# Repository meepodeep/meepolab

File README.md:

# MeepoLab
## Beginner 25-key midi controller with velocity-sensitive keys and drum pads

## Why does this exist
I made this project because I have been recently getting into making music for my own games, but I got tired of using a keyboard to do everything, so when Hackclub Stasis started to exist, I decided to make this. 
midi controller
# How to build
## PCB
1. Lay out and solder all of the smd components to the board
2. Solder the jst connectors
3. Solder the teensy on with pin headers
4. Flash the meepolab_sketch.ino file onto the teensy using midi mode
## Wiring 2
1. Solder the wires of the 12 pin jst connectors to all of the key matrix tactile switches and plug them into the plugs with these numbers. wire the "bottom" tactile switches to be the ones furthest from the pivot of the key, and the "top" ones closest to the center of the key. ( DO THIS AFTER YOU MOUNT THEM )
2. The V and ground are the 2 pins on the tactile switches, not actual voltage and ground
3. 
4. Solder the rest of your inputs, potentiometer, slide pot to the other 12pin jst connectors and plug them into the plugs with these numbers
5. 
6. Solder these jst connectors to the piezo drum pad sensors  and plug them into the plugs with these numbers
7. 
8. Solder the leds to the led jst connectors and plug them into the plugs with these numbers

## Assembly
1. assemble the 4 parts of the main shell and backplate together
2. Insert a bearing into the hole of every key
3. 
4. Align all of the keys how they are supposed to be and push the rod through the case,  bearings and keys
5. insert all of the return springs in between the pegs on the case and every key
6. 
7.insert all of the tactile switches into their holes in their mounting brackets.

8. tape piezo sensors to the back of each drum pad square on the drum pad membrane and the leds from the first shift register to it as well, and then mount the drum pad membrane to the keyboard
9. 
10. Mount the octave rocker, first by inserting it into position, and then inserting the axel after
11. 
12. insert a keyswitch into each of the octave rocker keyswitch mounts square holes and then screw them in using m3 hardware
13.
14. insert the keyswitches for the shift pause/play and record buttons into their holes
15. 
16. insert the potentiometers into their holes and screw them down using the included nut, after inserting the potentiometer area accent
17. 
18. put on the potentiometer caps
19. insert the slide potentiometers and screw in using m3 hardware after inserting accents
20. 
21. put on fader caps
22. insert leds and cover with optional acrylic
23. \
24. connect the cable to the teensy and run it through the hole
25. Attach bottom with m3 hardware
26. 
27. put keycaps on keys if you want
28. 

# BOM

|Name                |Purpose                                |Quantity|Total Cost (USD)|Link                                                                                                                                                                                                                                                                                                                                                                                                                                                                                                                                                                                                                                                                           |Distributor|
|--------------------|---------------------------------------|--------|----------------|-------------------------------------------------------------------------------------------------------------------------------------------------------------------------------------------------------------------------------------------------------------------------------------------------------------------------------------------------------------------------------------------------------------------------------------------------------------------------------------------------------------------------------------------------------------------------------------------------------------------------------------------------------------------------------|-----------|
|blue leds           |wie cool ist das bitte (it look pretty)|1       |1.42            |https://www.aliexpress.us/item/3256805214023855.html?spm=a2g0o.productlist.main.11.27da247cc44Ob9&algo_pvid=6ad9489b-c67a-4f82-b179-5dc6dc1113cd&algo_exp_id=6ad9489b-c67a-4f82-b179-5dc6dc1113cd-10&pdp_ext_f=%7B%22order%22%3A%22201%22%2C%22eval%22%3A%221%22%2C%22fromPage%22%3A%22search%22%7D&pdp_npi=6%40dis%21USD%211.54%211.54%21%21%211.54%211.54%21%40210319b017754310480521908e388a%2112000032909655679%21sea%21US%214381910819%21X%211%210%21n_tag%3A-29919%3Bd%3A747bdf24%3Bm03_new_user%3A-29895&curPageLogUid=ZzhfMunGS7JW&utparam-url=scene%3Asearch%7Cquery_from%3A%7Cx_object_id%3A1005005400338607%7C_p_origin_prod%3A                                     |aliexpress |
|acrylic             |optional led diffuse                   |1       |0.00            |                                                                                                                                                                                                                                                                                                                                                                                                                                                                                                                                                                                                                                                                               |i have     |
|keycap              |capping keys                           |3       |0.00            |                                                                                                                                                                                                                                                                                                                                                                                                                                                                                                                                                                                                                                                                               |i have     |
|m3 hardware         |hardware                               |1       |0.00            |                                                                                                                                                                                                                                                                                                                                                                                                                                                                                                                                                                                                                                                                               |i have     |
|mx keyswitches      |buttons                                |5       |0.00            |                                                                                                                                                                                                                                                                                                                                                                                                                                                                                                                                                                                                                                                                               |i have     |
|tactile swtiches    |For keys                               |3       |6.72            |https://www.aliexpress.us/item/2251832777534166.html?spm=a2g0o.productlist.main.18.2eb47bd6MNSk1R&algo_pvid=fd58ec73-369f-4c27-952a-6fe7ae065374&algo_exp_id=fd58ec73-369f-4c27-952a-6fe7ae065374-17&pdp_ext_f=%7B%22order%22%3A%22311%22%2C%22spu_best_type%22%3A%22price%22%2C%22eval%22%3A%221%22%2C%22fromPage%22%3A%22search%22%7D&pdp_npi=6%40dis%21USD%212.24%212.24%21%21%212.24%212.24%21%402101e2b217754281745518955efc8b%2166540730075%21sea%21US%214381910819%21X%211%210%21n_tag%3A-29919%3Bd%3A747bdf24%3Bm03_new_user%3A-29895&curPageLogUid=oJnjzIDFX0Vx&utparam-url=scene%3Asearch%7Cquery_from%3A%7Cx_object_id%3A32963848918%7C_p_origin_prod%3A            |aliexpress |
|12pin jst           |wiring keyswitches                     |3       |9.96            |https://www.aliexpress.us/item/3256811409118695.html?spm=a2g0o.detail.0.0.6681x6iXx6iXXv&mp=1&pdp_npi=6%40dis%21USD%21USD+10.11%21USD+4.42%21%21USD+4.09%21%21%21%4021033d1217779309699333617edbad%2112000056013353219%21ct%21US%214381910819%21%213%210%21&gatewayAdapt=glo2usa                                                                                                                                                                |aliexpress |
|Jst Ph2.0 2pin      |leds                                   |2       |5.36            |https://www.aliexpress.us/item/3256809537971085.html?spm=a2g0o.productlist.main.1.66a4xxW3xxW33G&algo_pvid=53bc2f55-a166-4808-bcda-89f28673fb9f&algo_exp_id=53bc2f55-a166-4808-bcda-89f28673fb9f-0&pdp_ext_f=%7B%22order%22%3A%22404%22%2C%22spu_best_type%22%3A%22price%22%2C%22eval%22%3A%221%22%2C%22fromPage%22%3A%22search%22%7D&pdp_npi=6%40dis%21USD%213.94%212.68%21%21%213.94%212.68%21%40210311cc17754258341333693e44fb%2112000049958235025%21sea%21US%214381910819%21X%211%210%21n_tag%3A-29919%3Bd%3A747bdf24%3Bm03_new_user%3A-29895&curPageLogUid=gRPF38s0QkMk&utparam-url=scene%3Asearch%7Cquery_from%3A%7Cx_object_id%3A1005009724285837%7C_p_origin_prod%3A   |aliexpress |
|Pcb                 |wiring up everythign                   |5       |28.60           |                                                                                                                                                                                                                                                                                                                                                                                                                                                                                                                                                                                                                                                                               |jlcpcb     |
|Teensy 4.1          |microcontroller                        |1       |31.50           |https://www.robotshop.com/products/teensy-41-usb-microcontroller-development-board-no-pins                                                                                                                                                                                                                                                                                                                                                                                                                                                                                                                                                                                     |RobotShop  |
|micro b to usb cable|cable for output                       |1       |2.34            |https://www.aliexpress.us/item/3256811607885785.html?spm=a2g0o.productlist.main.3.1e6bQvSEQvSEZj&algo_pvid=67884bd9-509c-4024-8bfe-0b6e9d9e573c&algo_exp_id=67884bd9-509c-4024-8bfe-0b6e9d9e573c-2&pdp_ext_f=%7B%22order%22%3A%2221%22%2C%22eval%22%3A%221%22%2C%22fromPage%22%3A%22search%22%7D&pdp_npi=6%40dis%21USD%214.36%212.01%21%21%2129.85%2113.76%21%40210311cc17752395169437863e44cf%2112000056573607707%21sea%21US%214381910819%21X%211%210%21n_tag%3A-29919%3Bd%3A5f7e402d%3Bm03_new_user%3A-29895%3BpisId%3A5000000203713564&curPageLogUid=mdmygZeXfOSF&utparam-url=scene%3Asearch%7Cquery_from%3A%7Cx_object_id%3A1005011794200537%7C_p_origin_prod%3A           |Aliexpress |
|45mm slide pot      |faders                                 |1       |2.63            |https://www.aliexpress.us/item/3256808869794293.html?spm=a2g0o.productlist.main.2.74107820OVm44F&algo_pvid=9917adf3-acb4-4790-a7cf-8f4ffd8a9d8e&algo_exp_id=9917adf3-acb4-4790-a7cf-8f4ffd8a9d8e-1&pdp_ext_f=%7B%22order%22%3A%22255%22%2C%22eval%22%3A%221%22%2C%22fromPage%22%3A%22search%22%7D&pdp_npi=6%40dis%21USD%216.27%212.63%21%21%2142.95%2118.04%21%402101f54117751893635285930efa7d%2112000047742701705%21sea%21US%214381910819%21X%211%210%21n_tag%3A-29919%3Bd%3A5f7e402d%3Bm03_new_user%3A-29895&curPageLogUid=GEGioSHPormD&utparam-url=scene%3Asearch%7Cquery_from%3A%7Cx_object_id%3A1005009056109045%7C_p_origin_prod%3A                                     |Aliexpress |
|10k pot             |dials                                  |2       |3.94            |https://www.aliexpress.us/item/3256802975243588.html?spm=a2g0o.productlist.main.2.7c453333dXrhMZ&algo_pvid=5c2d9dee-aaee-460d-8edb-a6a78972ec2f&algo_exp_id=5c2d9dee-aaee-460d-8edb-a6a78972ec2f-1&pdp_ext_f=%7B%22order%22%3A%221037%22%2C%22eval%22%3A%221%22%2C%22fromPage%22%3A%22search%22%7D&pdp_npi=6%40dis%21USD%212.08%211.96%21%21%212.08%211.96%21%40210337c117751859745701587eadbd%2112000024425220404%21sea%21US%214381910819%21X%211%210%21n_tag%3A-29919%3Bd%3A5f7e402d%3Bm03_new_user%3A-29895%3BpisId%3A5000000203818699&curPageLogUid=UUUgrKTkZwgk&utparam-url=scene%3Asearch%7Cquery_from%3A%7Cx_object_id%3A1005003161558340%7C_p_origin_prod%3A           |Aliexpress |
|Piezo sensor 12mm   |drum pads                              |1       |2.35            |https://www.aliexpress.us/item/3256806816727111.html?spm=a2g0o.productlist.main.7.43d97c70RlzFL1&algo_pvid=773ae987-53a6-4b90-81c1-8f194f19a3d9&algo_exp_id=773ae987-53a6-4b90-81c1-8f194f19a3d9-6&pdp_ext_f=%7B%22order%22%3A%221204%22%2C%22spu_best_type%22%3A%22price%22%2C%22eval%22%3A%221%22%2C%22fromPage%22%3A%22search%22%7D&pdp_npi=6%40dis%21USD%212.35%212.35%21%21%2116.09%2116.09%21%40210337c117751854355162761eadb5%2112000039015286338%21sea%21US%214381910819%21X%211%210%21n_tag%3A-29919%3Bd%3A5f7e402d%3Bm03_new_user%3A-29895&curPageLogUid=E22xylpVI4bu&utparam-url=scene%3Asearch%7Cquery_from%3A%7Cx_object_id%3A1005007003041863%7C_p_origin_prod%3A|Aliexpress |
|15x8mm spring       |key return                             |3       |13.48           |https://www.aliexpress.us/item/3256807447886846.html?spm=a2g0o.productlist.main.1.6c23783cb5SKfr&algo_pvid=ed966f8d-a3aa-4052-a5ed-c99569bf1975&algo_exp_id=ed966f8d-a3aa-4052-a5ed-c99569bf1975-0&pdp_ext_f=%7B%22order%22%3A%2272%22%2C%22eval%22%3A%221%22%2C%22fromPage%22%3A%22search%22%7D&pdp_npi=6%40dis%21USD%213.18%213.08%21%21%2121.81%2121.11%21%40210337c117751740330991406eadc8%2112000041585331673%21sea%21US%214381910819%21X%211%210%21n_tag%3A-29919%3Bd%3A5f7e402d%3Bm03_new_user%3A-29895&curPageLogUid=wyxdnGUcsvBT&utparam-url=scene%3Asearch%7Cquery_from%3A%7Cx_object_id%3A1005007634201598%7C_p_origin_prod%3A                                      |Aliexpress |
|6X10X3 bearing      |key bearings                           |3       |13.95           |https://www.aliexpress.us/item/3256810378046508.html?spm=a2g0o.productlist.main.7.22243b11uhPXbH&algo_pvid=685b833c-7b74-4b83-a32a-719ad60603e5&algo_exp_id=685b833c-7b74-4b83-a32a-719ad60603e5-6&pdp_ext_f=%7B%22order%22%3A%22509%22%2C%22eval%22%3A%221%22%2C%22fromPage%22%3A%22search%22%7D&pdp_npi=6%40dis%21USD%213.81%213.79%21%21%2126.08%2125.92%21%4021030a4b17751710399248378e75a4%2112000052831084350%21sea%21US%214381910819%21X%211%210%21n_tag%3A-29919%3Bd%3A5f7e402d%3Bm03_new_user%3A-29895&curPageLogUid=wu6zyN0LX0XR&utparam-url=scene%3Asearch%7Cquery_from%3A%7Cx_object_id%3A1005010564361260%7C_p_origin_prod%3A                                     |aliexpress |
|74HC595S16-13       |shift register for leds                |4       |1.44            |https://www.digikey.com/en/products/detail/diodes-incorporated/74HC595S16-13/24630355                                                                                                                                                                                                                                                                                                                                                                                                                                                                                                                                                                                          |Digikey    |
|RC0402FR-071ML      |resistor for piezo                     |10      |0.03            |https://www.digikey.com/en/products/detail/yageo/RC0402FR-071ML/726515                                                                                                                                                                                                                                                                                                                                                                                                                                                                                                                                                                                                         |Digikey    |
|CRT0805-BY-1500ELF  |Resistor for multiplexers              |2       |0.74            |https://www.digikey.com/en/products/detail/bourns-inc/CRT0805-BY-1500ELF/2564111                                                                                                                                                                                                                                                                                                                                                                                                                                                                                                                                                                                               |Digikey    |
|1N4148WS            |Key grid diode                         |70      |3.64            |https://www.digikey.com/en/products/detail/evvo/1N4148WS/21407535                                                                                                                                                                                                                                                                                                                                                                                                                                                                                                                                                                                                              |Digikey    |
|MMSZ4684T1G         |zener diode for piezo sensors          |10      |0.79            |https://www.digikey.com/en/products/detail/onsemi/MMSZ4684T1G/919718                                                                                                                                                                                                                                                                                                                                                                                                                                                                                                                                                                                             |Digikey    |
|SD103AW-7-F         |Schottky diode for piezo sensors       |20      |1.60            |https://www.digikey.com/en/products/detail/diodes-incorporated/SD103AW-7-F/1306103                                                                                                                                                                                                                                                                                                                                                                                                                                                                                                                                                                                             |Digikey    |
|4.7 nf capacitor    |Pcb                                    |10      |2.81            |https://www.digikey.com/en/products/detail/murata-electronics/GRM31BR72J472KW01L/789415                                                                                                                                                                                                                                                                                                                                                                                                                                                                                                                                                                                        |Digikey    |
|0.1uf capacitor     |pcb                                    |10      |0.12            |https://www.digikey.com/en/products/detail/murata-electronics/GRM033C71C104KE14D/5026260                                                                                                                                                                                                                                                                                                                                                                                                                                                                                                                                                                                       |Digikey    |

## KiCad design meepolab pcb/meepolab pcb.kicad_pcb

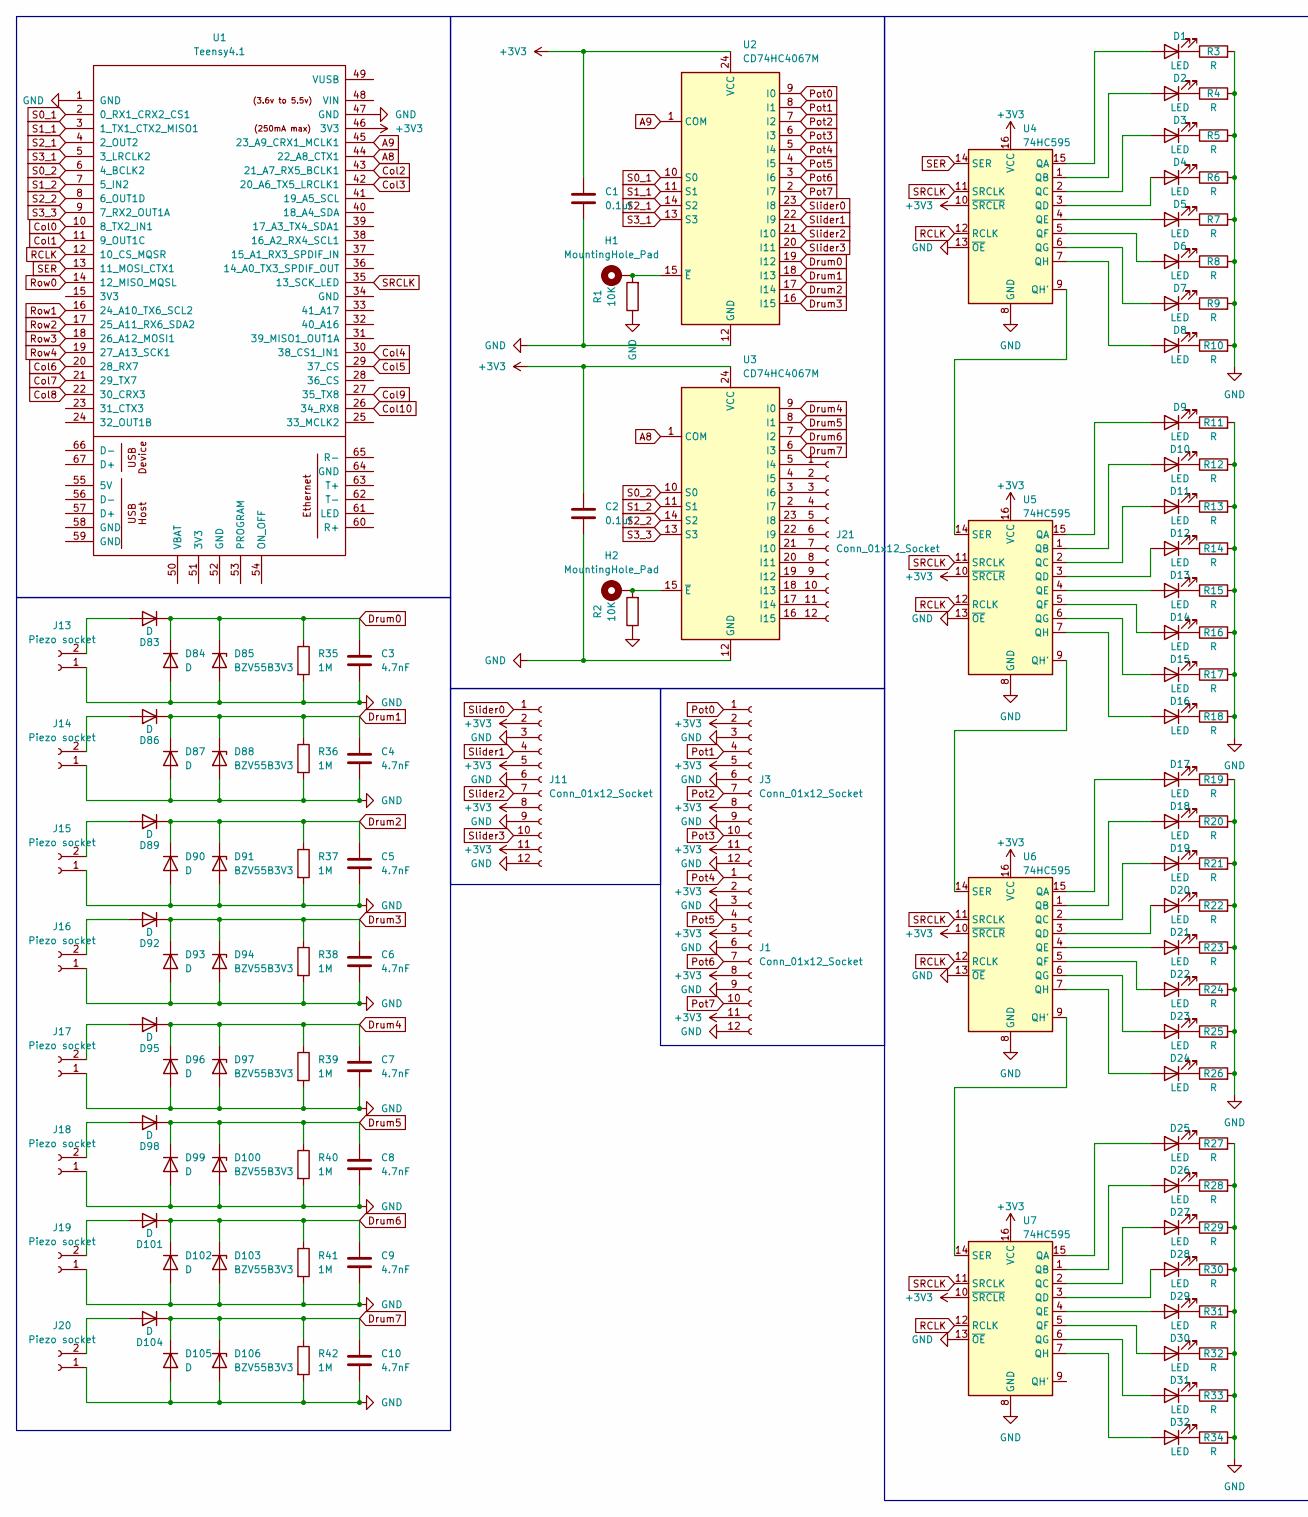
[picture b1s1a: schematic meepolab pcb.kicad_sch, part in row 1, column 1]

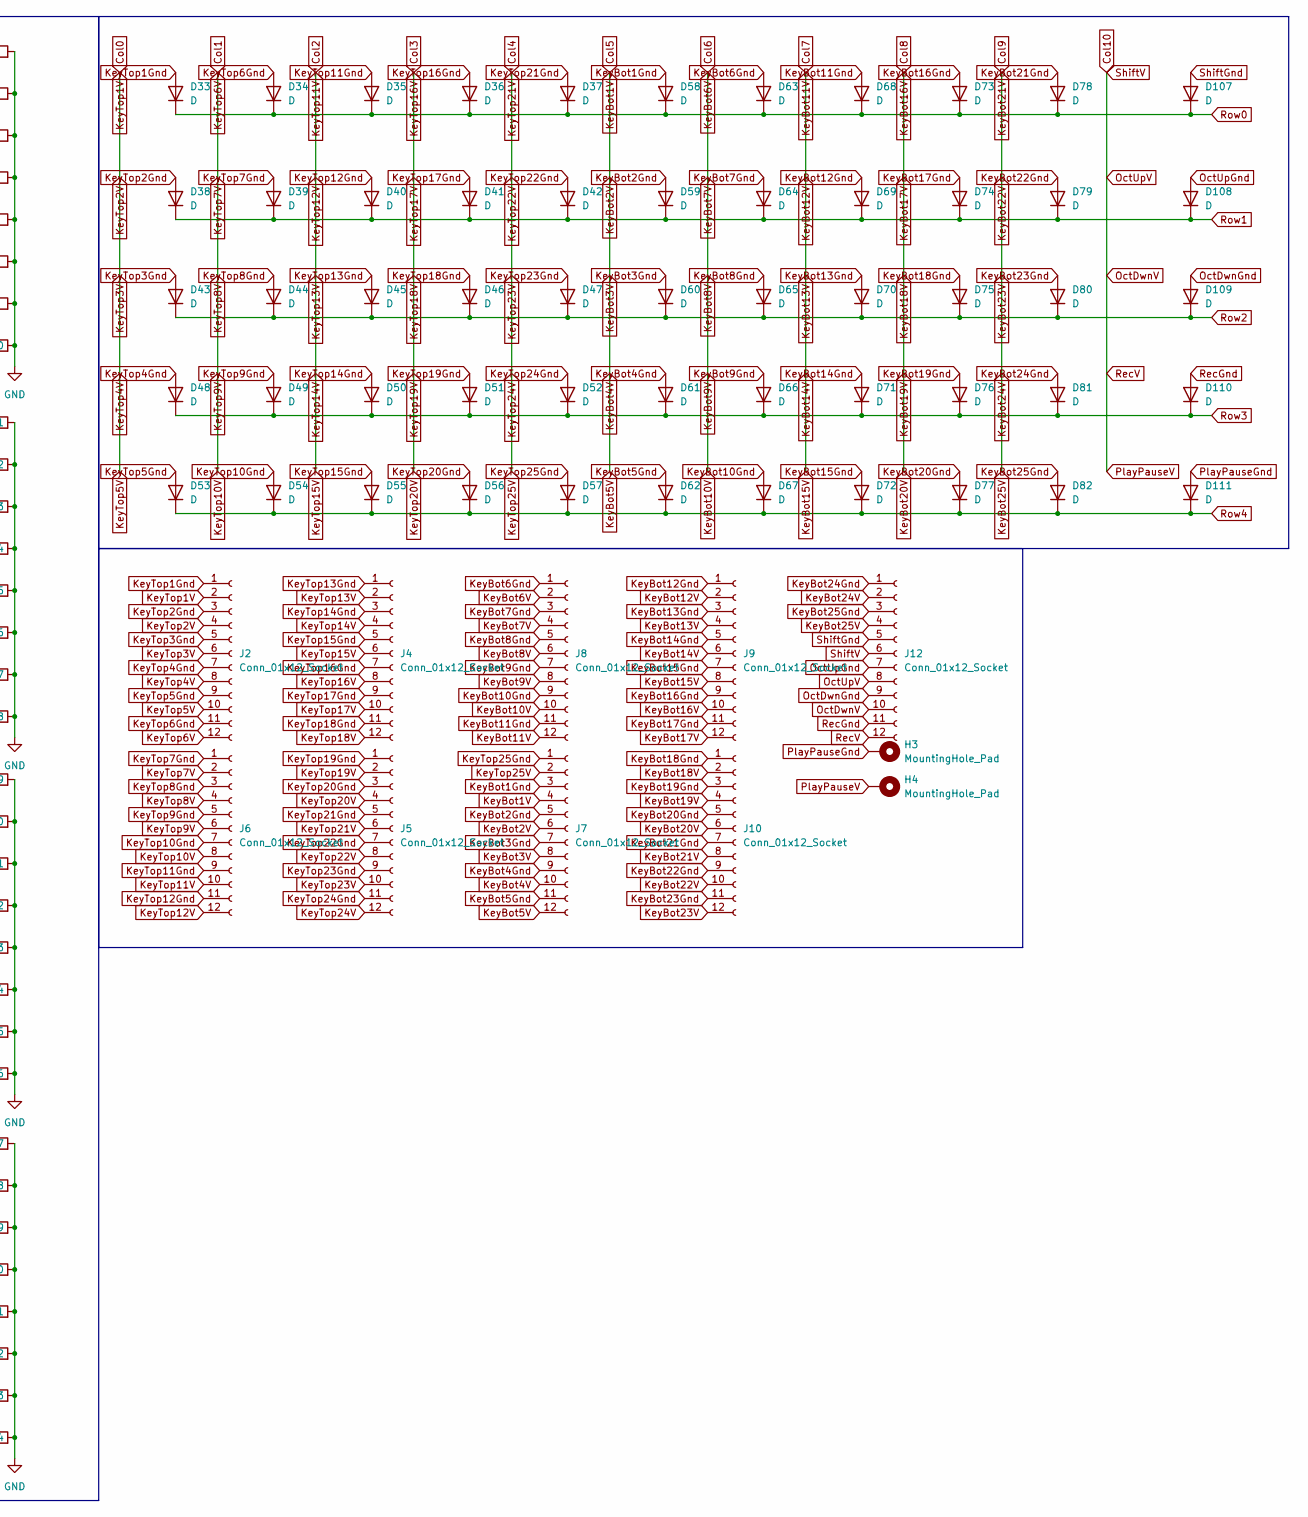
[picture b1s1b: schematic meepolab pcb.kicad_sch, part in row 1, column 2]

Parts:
C1, C2: 0.1uf; C_0201_0603Metric
C3, C4, C5, C6, C7, C8, C9, C10: 4.7nF; C_0201_0603Metric
D1, D2, D3, D4, D5, D6, D7, D8, D9, D10, D11, D12, D13, D14, D15, D16, D17, D18, D19, D20, D21, D22, D23, D24, D25, D26, D27, D28, D29, D30, D31, D32: LED; JST_EH_B2B-EH-A_1x02_P2.50mm_Vertical
D33, D34, D35, D36, D37, D38, D39, D40, D41, D42, D43, D44, D45, D46, D47, D48, D49, D50, D51, D52, D53, D54, D55, D56, D57, D58, D59, D60, D61, D62, D63, D64, D65, D66, D67, D68, D69, D70, D71, D72, D73, D74, D75, D76, D77, D78, D79, D80, D81, D82, D107, D108, D109, D110, D111: D; D_SOD-323
D83, D84, D86, D87, D89, D90, D92, D93, D95, D96, D98, D99, D101, D102, D104, D105: D; D_SOD-123
D85, D88, D91, D94, D97, D100, D103, D106: BZV55B3V3; D_SOD-123
H1, H2, H3, H4: MountingHole_Pad; TestPoint_Pad_1.0x1.0mm
J1, J2, J3, J4, J5, J6, J7, J8, J9, J10, J11, J12, J21: Conn_01x12_Socket; JST_EH_B12B-EH-A_1x12_P2.50mm_Vertical
J13, J14, J15, J16, J17, J18, J19, J20: Piezo socket; JST_EH_B2B-EH-A_1x02_P2.50mm_Vertical
R1, R2: 10K; R_0805_2012Metric
R3, R4, R5, R6, R7, R8, R9, R10, R11, R12, R13, R14, R15, R16, R17, R18, R19, R20, R21, R22, R23, R24, R25, R26, R27, R28, R29, R30, R31, R32, R33, R34: R; R_0402_1005Metric
R35, R36, R37, R38, R39, R40, R41, R42: 1M; R_0402_1005Metric
U1: Teensy4.1; Teensy41
U2, U3: CD74HC4067M; SOIC-24W_7.5x15.4mm_P1.27mm
U4, U5, U6, U7: 74HC595; SOIC-16_3.9x9.9mm_P1.27mm

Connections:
+3V3: C1.1, C2.1, J1.2, J1.5, J1.8, J1.11, J3.2, J3.5, J3.8, J3.11, J11.2, J11.5, J11.8, J11.11, U1.46 (3V3), U2.24 (VCC), U3.24 (VCC), U4.10 (~SRCLR), U4.16 (VCC), U5.10 (~SRCLR), U5.16 (VCC), U6.10 (~SRCLR), U6.16 (VCC), U7.10 (~SRCLR), U7.16 (VCC)
A8: U1.44 (22_A8_CTX1), U3.1 (COM)
A9: U1.45 (23_A9_CRX1_MCLK1), U2.1 (COM)
Col0: J2.2, J2.4, J2.6, J2.8, J2.10, U1.10 (8_TX2_IN1)
Col1: J2.12, J6.2, J6.4, J6.6, J6.8, U1.11 (9_OUT1C)
Col2: J4.2, J4.4, J4.6, J6.10, J6.12, U1.43 (21_A7_RX5_BCLK1)
Col3: J4.8, J4.10, J4.12, J5.2, J5.4, U1.42 (20_A6_TX5_LRCLK1)
Col4: J5.6, J5.8, J5.10, J5.12, J7.2, U1.30 (38_CS1_IN1)
Col5: J7.4, J7.6, J7.8, J7.10, J7.12, U1.29 (37_CS)
Col6: J8.2, J8.4, J8.6, J8.8, J8.10, U1.20 (28_RX7)
Col7: J8.12, J9.2, J9.4, J9.6, J9.8, U1.21 (29_TX7)
Col8: J9.10, J9.12, J10.2, J10.4, J10.6, U1.22 (30_CRX3)
Col9: J10.8, J10.10, J10.12, J12.2, J12.4, U1.27 (35_TX8)
Col10: H4.1, J12.6, J12.8, J12.10, J12.12, U1.26 (34_RX8)
Drum0: C3.1, D83.1 (K), D84.1 (K), D85.1 (K), R35.1, U2.19 (I12)
Drum1: C4.1, D86.1 (K), D87.1 (K), D88.1 (K), R36.1, U2.18 (I13)
Drum2: C5.1, D89.1 (K), D90.1 (K), D91.1 (K), R37.1, U2.17 (I14)
Drum3: C6.1, D92.1 (K), D93.1 (K), D94.1 (K), R38.1, U2.16 (I15)
Drum4: C7.1, D95.1 (K), D96.1 (K), D97.1 (K), R39.1, U3.9 (I0)
Drum5: C8.1, D98.1 (K), D99.1 (K), D100.1 (K), R40.1, U3.8 (I1)
Drum6: C9.1, D101.1 (K), D102.1 (K), D103.1 (K), R41.1, U3.7 (I2)
Drum7: C10.1, D104.1 (K), D105.1 (K), D106.1 (K), R42.1, U3.6 (I3)
GND: C1.2, C2.2, C3.2, C4.2, C5.2, C6.2, C7.2, C8.2, C9.2, C10.2, D84.2 (A), D85.2 (A), D87.2 (A), D88.2 (A), D90.2 (A), D91.2 (A), D93.2 (A), D94.2 (A), D96.2 (A), D97.2 (A), D99.2 (A), D100.2 (A), D102.2 (A), D103.2 (A), D105.2 (A), D106.2 (A), J1.3, J1.6, J1.9, J1.12, J3.3, J3.6, J3.9, J3.12, J11.3, J11.6, J11.9, J11.12, J13.1, J14.1, J15.1, J16.1, J17.1, J18.1, J19.1, J20.1, R1.1, R2.1, R3.2, R4.2, R5.2, R6.2, R7.2, R8.2, R9.2, R10.2, R11.2, R12.2, R13.2, R14.2, R15.2, R16.2, R17.2, R18.2, R19.2, R20.2, R21.2, R22.2, R23.2, R24.2, R25.2, R26.2, R27.2, R28.2, R29.2, R30.2, R31.2, R32.2, R33.2, R34.2, R35.2, R36.2, R37.2, R38.2, R39.2, R40.2, R41.2, R42.2, U1.1 (GND), U1.47 (GND), U2.12 (GND), U3.12 (GND), U4.8 (GND), U4.13 (~OE), U5.8 (GND), U5.13 (~OE), U6.8 (GND), U6.13 (~OE), U7.8 (GND), U7.13 (~OE)
KeyBot1Gnd: D58.2 (A), J7.3
KeyBot2Gnd: D59.2 (A), J7.5
KeyBot3Gnd: D60.2 (A), J7.7
KeyBot4Gnd: D61.2 (A), J7.9
KeyBot5Gnd: D62.2 (A), J7.11
KeyBot6Gnd: D63.2 (A), J8.1
KeyBot7Gnd: D64.2 (A), J8.3
KeyBot8Gnd: D65.2 (A), J8.5
KeyBot9Gnd: D66.2 (A), J8.7
KeyBot10Gnd: D67.2 (A), J8.9
KeyBot11Gnd: D68.2 (A), J8.11
KeyBot12Gnd: D69.2 (A), J9.1
KeyBot13Gnd: D70.2 (A), J9.3
KeyBot14Gnd: D71.2 (A), J9.5
KeyBot15Gnd: D72.2 (A), J9.7
KeyBot16Gnd: D73.2 (A), J9.9
KeyBot17Gnd: D74.2 (A), J9.11
KeyBot18Gnd: D75.2 (A), J10.1
KeyBot19Gnd: D76.2 (A), J10.3
KeyBot20Gnd: D77.2 (A), J10.5
KeyBot21Gnd: D78.2 (A), J10.7
KeyBot22Gnd: D79.2 (A), J10.9
KeyBot23Gnd: D80.2 (A), J10.11
KeyBot24Gnd: D81.2 (A), J12.1
KeyBot25Gnd: D82.2 (A), J12.3
KeyTop1Gnd: D33.2 (A), J2.1
KeyTop2Gnd: D38.2 (A), J2.3
KeyTop3Gnd: D43.2 (A), J2.5
KeyTop4Gnd: D48.2 (A), J2.7
KeyTop5Gnd: D53.2 (A), J2.9
KeyTop6Gnd: D34.2 (A), J2.11
KeyTop7Gnd: D39.2 (A), J6.1
KeyTop8Gnd: D44.2 (A), J6.3
KeyTop9Gnd: D49.2 (A), J6.5
KeyTop10Gnd: D54.2 (A), J6.7
KeyTop11Gnd: D35.2 (A), J6.9
KeyTop12Gnd: D40.2 (A), J6.11
KeyTop13Gnd: D45.2 (A), J4.1
KeyTop14Gnd: D50.2 (A), J4.3
KeyTop15Gnd: D55.2 (A), J4.5
KeyTop16Gnd: D36.2 (A), J4.7
KeyTop17Gnd: D41.2 (A), J4.9
KeyTop18Gnd: D46.2 (A), J4.11
KeyTop19Gnd: D51.2 (A), J5.1
KeyTop20Gnd: D56.2 (A), J5.3
KeyTop21Gnd: D37.2 (A), J5.5
KeyTop22Gnd: D42.2 (A), J5.7
KeyTop23Gnd: D47.2 (A), J5.9
KeyTop24Gnd: D52.2 (A), J5.11
KeyTop25Gnd: D57.2 (A), J7.1
unnamed: D1.2 (A), U4.15 (QA)
unnamed: D1.1 (K), R3.1
unnamed: D2.2 (A), U4.1 (QB)
unnamed: D2.1 (K), R4.1
unnamed: D3.2 (A), U4.2 (QC)
unnamed: D3.1 (K), R5.1
unnamed: D4.2 (A), U4.3 (QD)
unnamed: D4.1 (K), R6.1
unnamed: D5.2 (A), U4.4 (QE)
unnamed: D5.1 (K), R7.1
unnamed: D6.2 (A), U4.5 (QF)
unnamed: D6.1 (K), R8.1
unnamed: D7.2 (A), U4.6 (QG)
unnamed: D7.1 (K), R9.1
unnamed: D8.2 (A), U4.7 (QH)
unnamed: D8.1 (K), R10.1
unnamed: D9.2 (A), U5.15 (QA)
unnamed: D9.1 (K), R11.1
unnamed: D10.2 (A), U5.1 (QB)
unnamed: D10.1 (K), R12.1
unnamed: D11.2 (A), U5.2 (QC)
unnamed: D11.1 (K), R13.1
unnamed: D12.2 (A), U5.3 (QD)
unnamed: D12.1 (K), R14.1
unnamed: D13.2 (A), U5.4 (QE)
unnamed: D13.1 (K), R15.1
unnamed: D14.2 (A), U5.5 (QF)
unnamed: D14.1 (K), R16.1
unnamed: D15.2 (A), U5.6 (QG)
unnamed: D15.1 (K), R17.1
unnamed: D16.2 (A), U5.7 (QH)
unnamed: D16.1 (K), R18.1
unnamed: D17.2 (A), U6.15 (QA)
unnamed: D17.1 (K), R19.1
unnamed: D18.2 (A), U6.1 (QB)
unnamed: D18.1 (K), R20.1
unnamed: D19.2 (A), U6.2 (QC)
unnamed: D19.1 (K), R21.1
unnamed: D20.2 (A), U6.3 (QD)
unnamed: D20.1 (K), R22.1
unnamed: D21.2 (A), U6.4 (QE)
unnamed: D21.1 (K), R23.1
unnamed: D22.2 (A), U6.5 (QF)
unnamed: D22.1 (K), R24.1
unnamed: D23.2 (A), U6.6 (QG)
unnamed: D23.1 (K), R25.1
unnamed: D24.2 (A), U6.7 (QH)
unnamed: D24.1 (K), R26.1
unnamed: D25.2 (A), U7.15 (QA)
unnamed: D25.1 (K), R27.1
unnamed: D26.2 (A), U7.1 (QB)
unnamed: D26.1 (K), R28.1
unnamed: D27.2 (A), U7.2 (QC)
unnamed: D27.1 (K), R29.1
unnamed: D28.2 (A), U7.3 (QD)
unnamed: D28.1 (K), R30.1
unnamed: D29.2 (A), U7.4 (QE)
unnamed: D29.1 (K), R31.1
unnamed: D30.2 (A), U7.5 (QF)
unnamed: D30.1 (K), R32.1
unnamed: D31.2 (A), U7.6 (QG)
unnamed: D31.1 (K), R33.1
unnamed: D32.2 (A), U7.7 (QH)
unnamed: D32.1 (K), R34.1
unnamed: D83.2 (A), J13.2
unnamed: D86.2 (A), J14.2
unnamed: D89.2 (A), J15.2
unnamed: D92.2 (A), J16.2
unnamed: D95.2 (A), J17.2
unnamed: D98.2 (A), J18.2
unnamed: D101.2 (A), J19.2
unnamed: D104.2 (A), J20.2
unnamed: J21.1, U3.5 (I4)
unnamed: J21.2, U3.4 (I5)
unnamed: J21.3, U3.3 (I6)
unnamed: J21.4, U3.2 (I7)
unnamed: J21.5, U3.23 (I8)
unnamed: J21.6, U3.22 (I9)
unnamed: J21.7, U3.21 (I10)
unnamed: J21.8, U3.20 (I11)
unnamed: J21.9, U3.19 (I12)
unnamed: J21.10, U3.18 (I13)
unnamed: J21.11, U3.17 (I14)
unnamed: J21.12, U3.16 (I15)
unnamed: H1.1, R1.2, U2.15 (~E)
unnamed: H2.1, R2.2, U3.15 (~E)
unnamed: U4.9 (QH'), U5.14 (SER)
unnamed: U5.9 (QH'), U6.14 (SER)
unnamed: U6.9 (QH'), U7.14 (SER)
OctDwnGnd: D109.2 (A), J12.9
OctUpGnd: D108.2 (A), J12.7
PlayPauseGnd: D111.2 (A), H3.1
Pot0: J3.1, U2.9 (I0)
Pot1: J3.4, U2.8 (I1)
Pot2: J3.7, U2.7 (I2)
Pot3: J3.10, U2.6 (I3)
Pot4: J1.1, U2.5 (I4)
Pot5: J1.4, U2.4 (I5)
Pot6: J1.7, U2.3 (I6)
Pot7: J1.10, U2.2 (I7)
RCLK: U1.12 (10_CS_MQSR), U4.12 (RCLK), U5.12 (RCLK), U6.12 (RCLK), U7.12 (RCLK)
RecGnd: D110.2 (A), J12.11
Row0: D33.1 (K), D34.1 (K), D35.1 (K), D36.1 (K), D37.1 (K), D58.1 (K), D63.1 (K), D68.1 (K), D73.1 (K), D78.1 (K), D107.1 (K), U1.14 (12_MISO_MQSL)
Row1: D38.1 (K), D39.1 (K), D40.1 (K), D41.1 (K), D42.1 (K), D59.1 (K), D64.1 (K), D69.1 (K), D74.1 (K), D79.1 (K), D108.1 (K), U1.16 (24_A10_TX6_SCL2)
Row2: D43.1 (K), D44.1 (K), D45.1 (K), D46.1 (K), D47.1 (K), D60.1 (K), D65.1 (K), D70.1 (K), D75.1 (K), D80.1 (K), D109.1 (K), U1.17 (25_A11_RX6_SDA2)
Row3: D48.1 (K), D49.1 (K), D50.1 (K), D51.1 (K), D52.1 (K), D61.1 (K), D66.1 (K), D71.1 (K), D76.1 (K), D81.1 (K), D110.1 (K), U1.18 (26_A12_MOSI1)
Row4: D53.1 (K), D54.1 (K), D55.1 (K), D56.1 (K), D57.1 (K), D62.1 (K), D67.1 (K), D72.1 (K), D77.1 (K), D82.1 (K), D111.1 (K), U1.19 (27_A13_SCK1)
S0_1: U1.2 (0_RX1_CRX2_CS1), U2.10 (S0)
S0_2: U1.6 (4_BCLK2), U3.10 (S0)
S1_1: U1.3 (1_TX1_CTX2_MISO1), U2.11 (S1)
S1_2: U1.7 (5_IN2), U3.11 (S1)
S2_1: U1.4 (2_OUT2), U2.14 (S2)
S2_2: U1.8 (6_OUT1D), U3.14 (S2)
S3_1: U1.5 (3_LRCLK2), U2.13 (S3)
S3_3: U1.9 (7_RX2_OUT1A), U3.13 (S3)
SER: U1.13 (11_MOSI_CTX1), U4.14 (SER)
SRCLK: U1.35 (13_SCK_LED), U4.11 (SRCLK), U5.11 (SRCLK), U6.11 (SRCLK), U7.11 (SRCLK)
ShiftGnd: D107.2 (A), J12.5
Slider0: J11.1, U2.23 (I8)
Slider1: J11.4, U2.22 (I9)
Slider2: J11.7, U2.21 (I10)
Slider3: J11.10, U2.20 (I11)

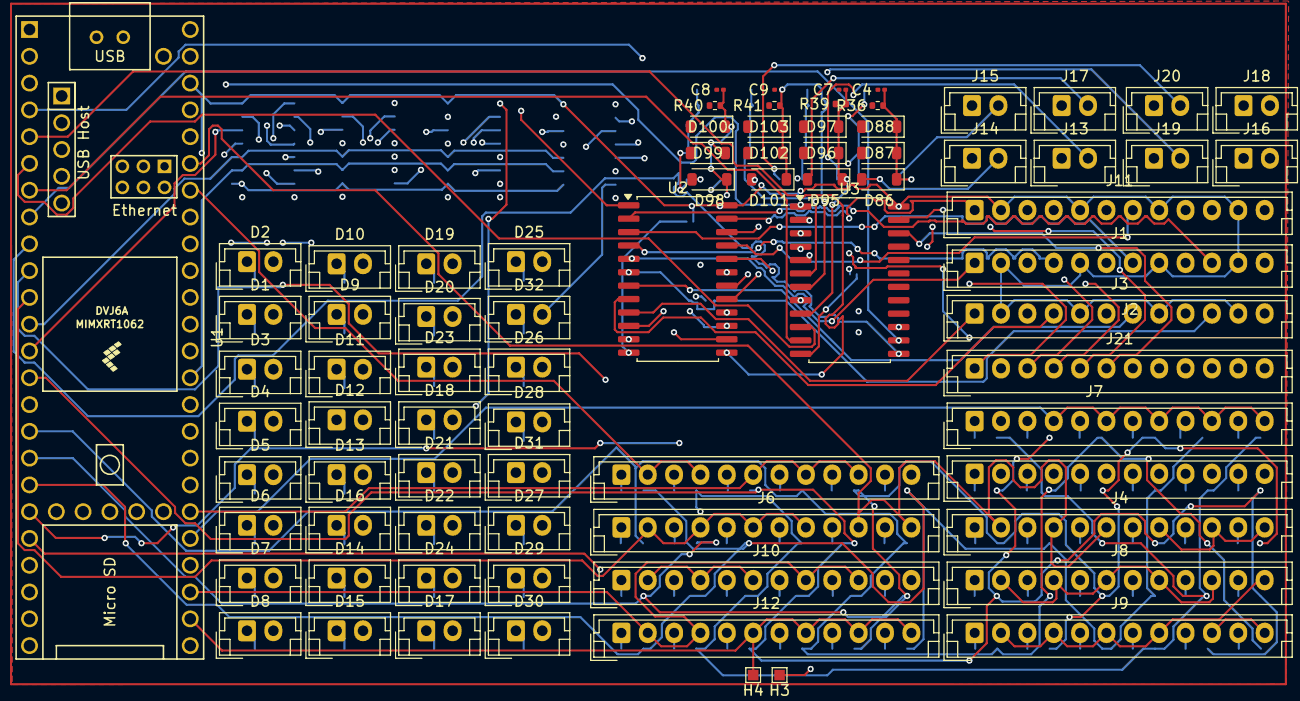
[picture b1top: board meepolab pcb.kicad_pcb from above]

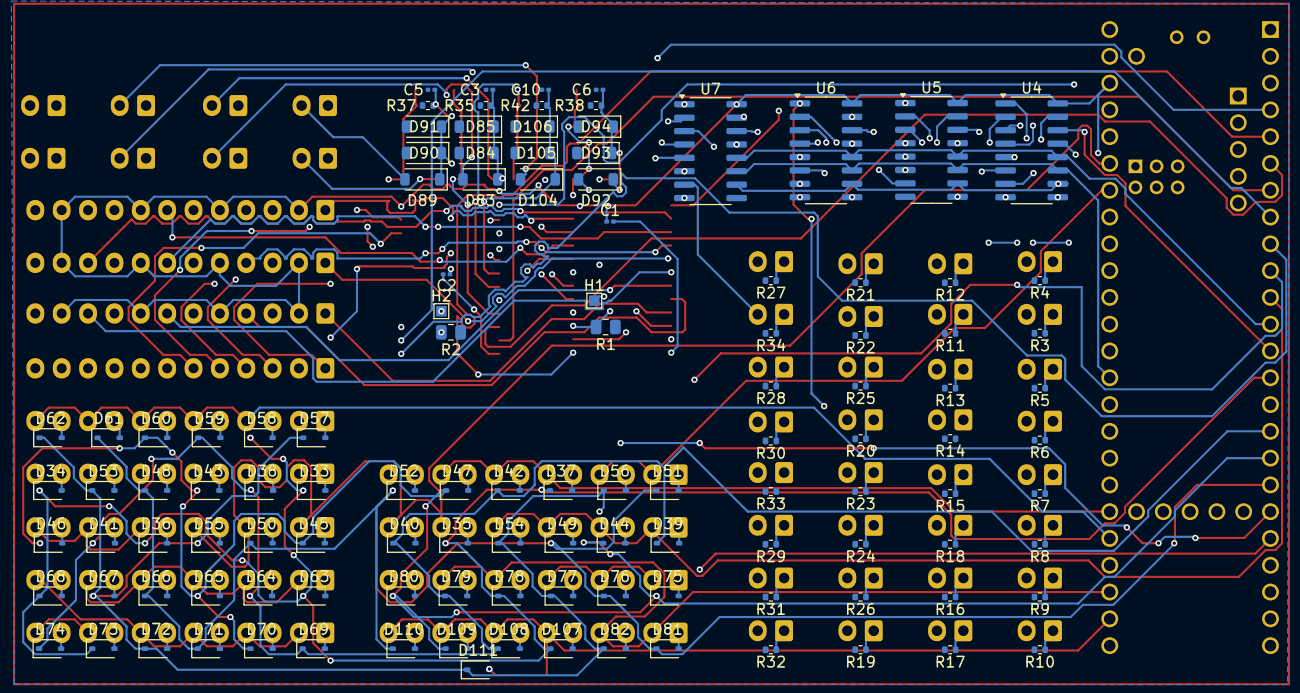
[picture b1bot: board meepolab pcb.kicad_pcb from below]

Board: 4 copper layers, 195 parts (117 on the bottom side), 195 nets.

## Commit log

2026-03-31 made schematic and started pcb
2026-04-01 wokred on routing
2026-04-02 worked on layout
2026-04-05 wawwa
2026-04-06 Added Cad files
2026-04-06 added led cods
2026-06-28 updated cad
2026-06-28 wawaw
